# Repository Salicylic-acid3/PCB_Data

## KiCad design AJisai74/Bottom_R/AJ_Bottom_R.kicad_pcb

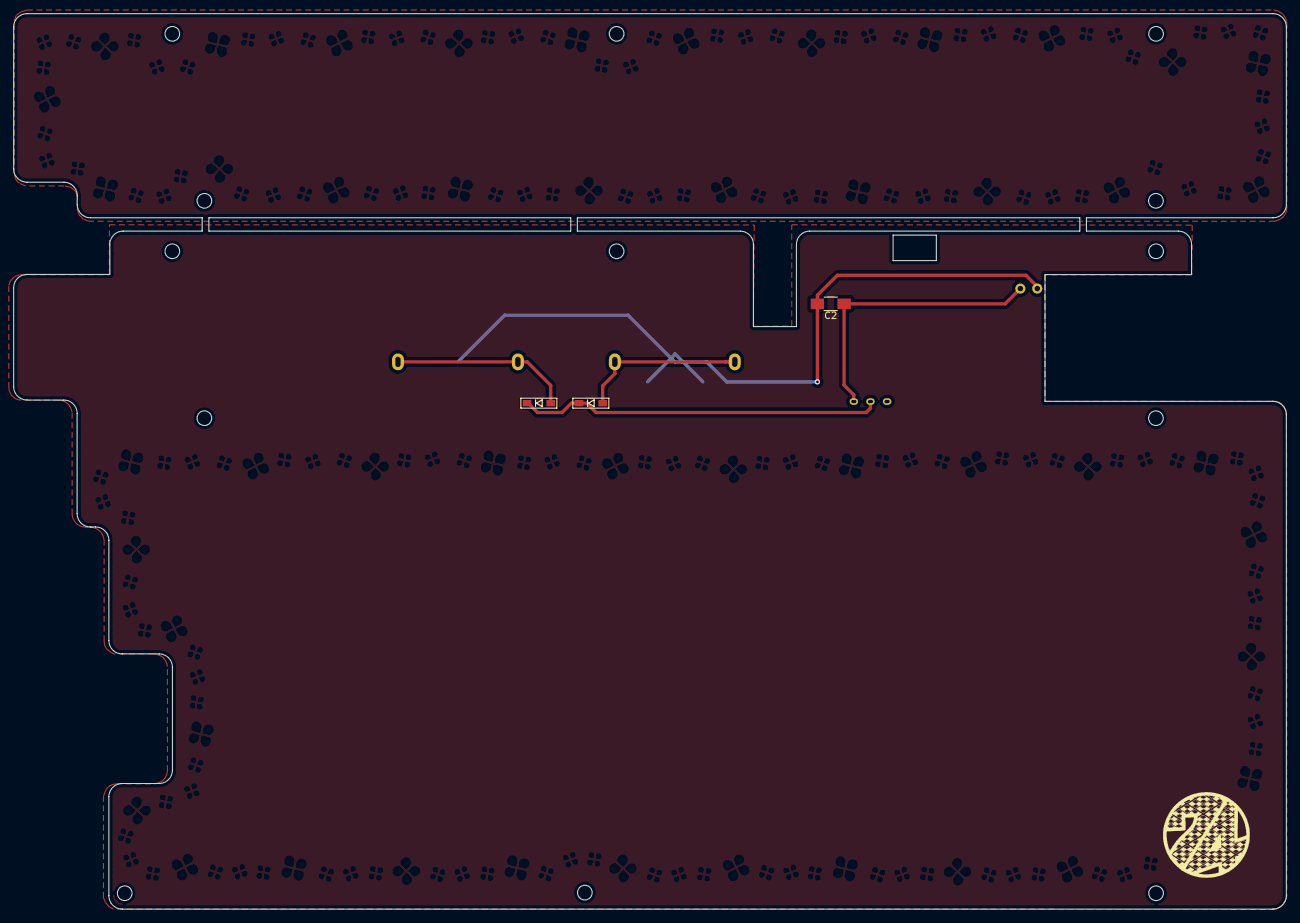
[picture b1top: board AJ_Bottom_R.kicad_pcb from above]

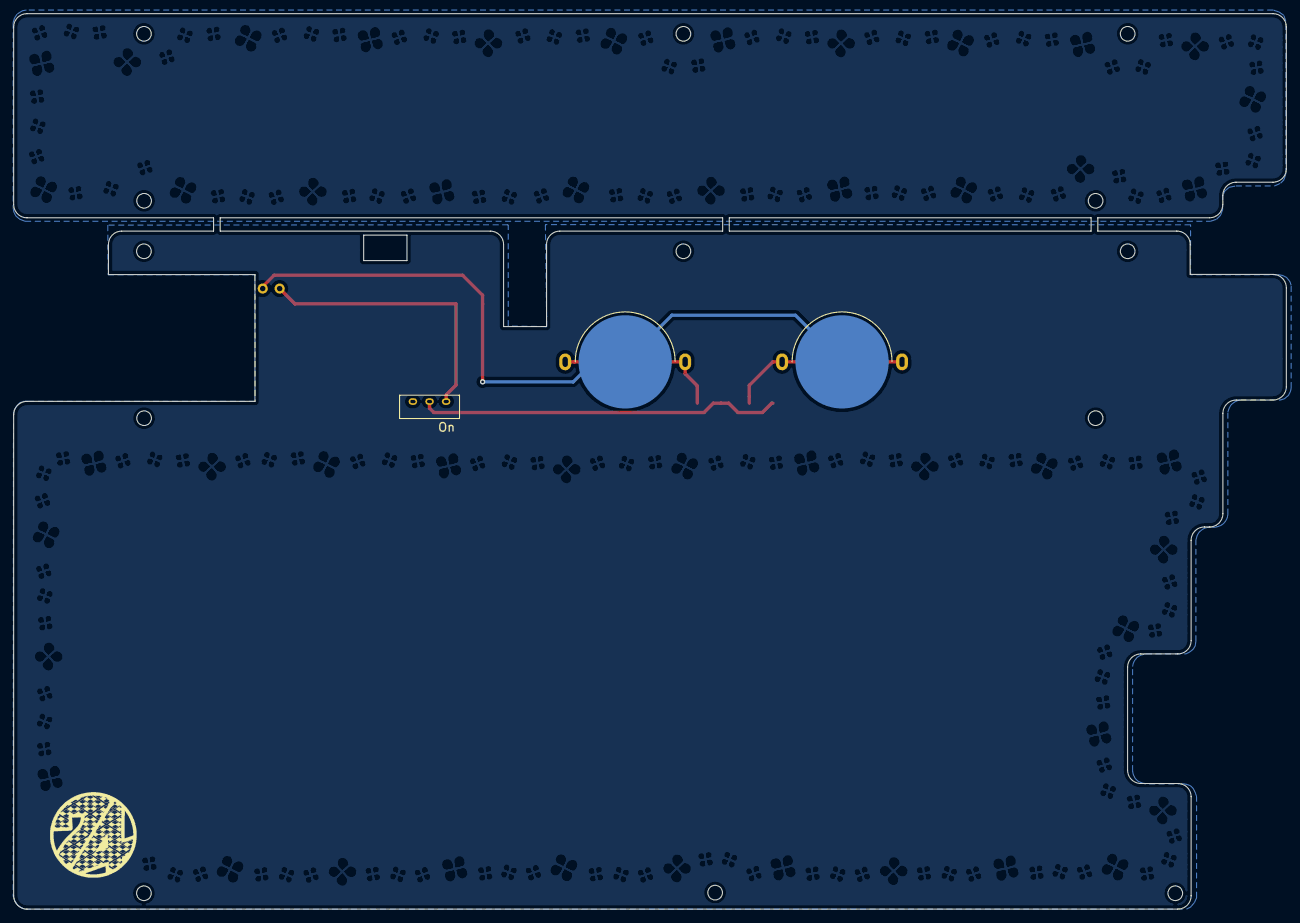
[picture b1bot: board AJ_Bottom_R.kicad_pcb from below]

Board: 2 copper layers, 191.0 x 134.4 mm, 20 parts (6 on the bottom side), 5 nets.

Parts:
BT3, BT4: Battery_Cell; ali_CR1632
C2: C_Small; C_1206_HandSoldering_Back
D3, D4: D; D3_SMD_L1
J4, J5, J13, J14, J15, J16, J18, J19, J19#2: Conn_01x01; HOLE_m2
J20: Conn_01x02; 2pinBLE
Ref**: Val**; HOLE_m2
Ref**#2, Ref**#3, Ref**#4: Val**; HOLE_m2
SW2: SW_Push_SPDT; MSK-12D19

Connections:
Bat+: C2.1, J20.1, SW2.1
GND: BT3.2, BT4.2, C2.2, J20.2
unnamed: BT3.1, D3.2
unnamed: BT4.1, D4.2
unnamed: D3.1, D4.1, SW2.2

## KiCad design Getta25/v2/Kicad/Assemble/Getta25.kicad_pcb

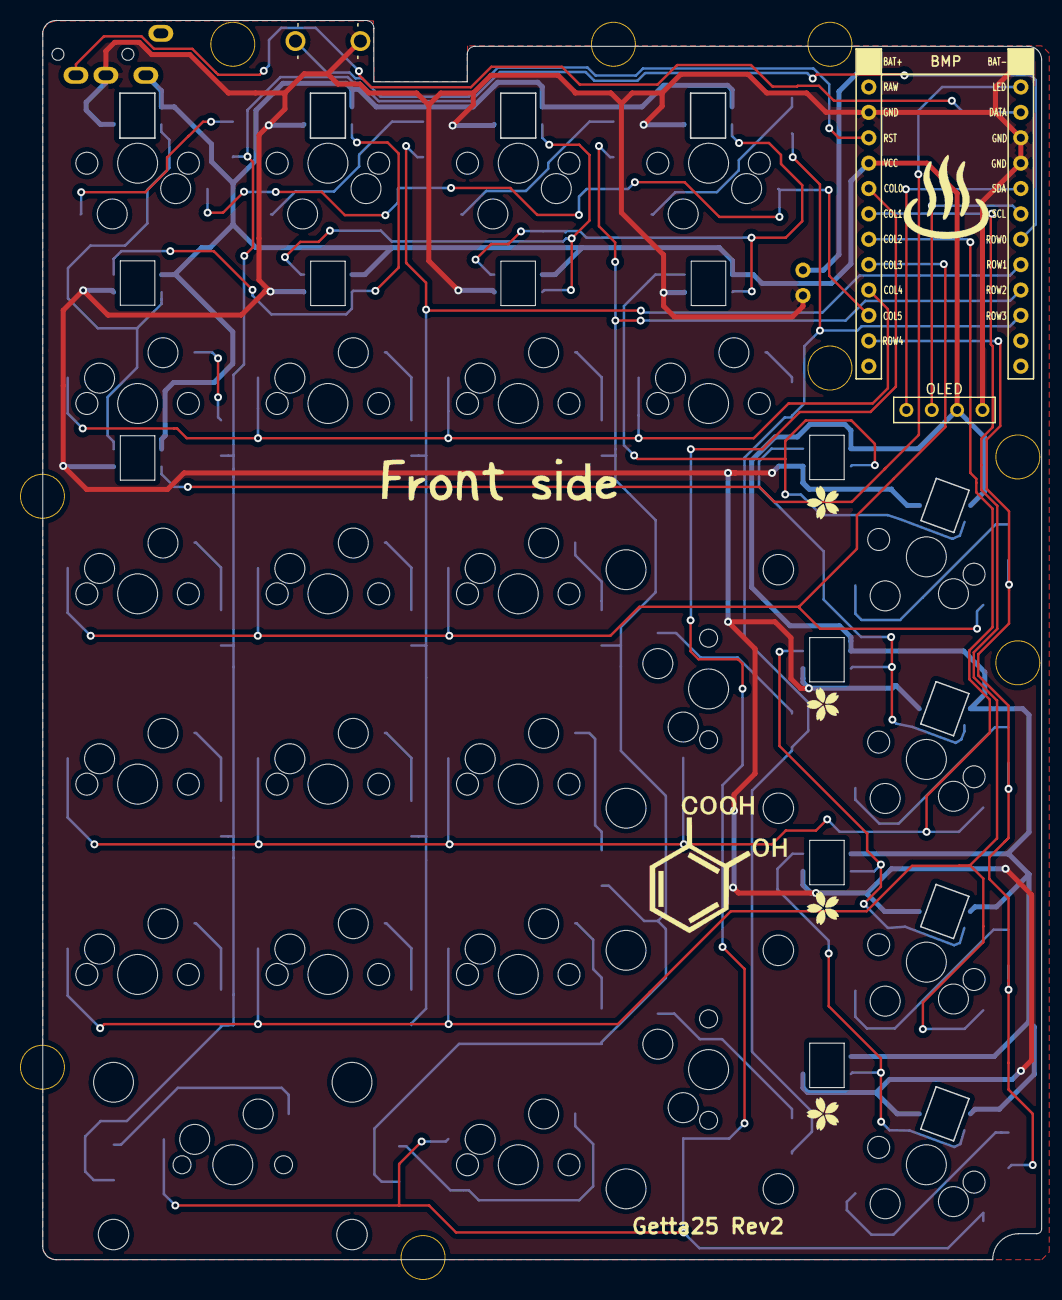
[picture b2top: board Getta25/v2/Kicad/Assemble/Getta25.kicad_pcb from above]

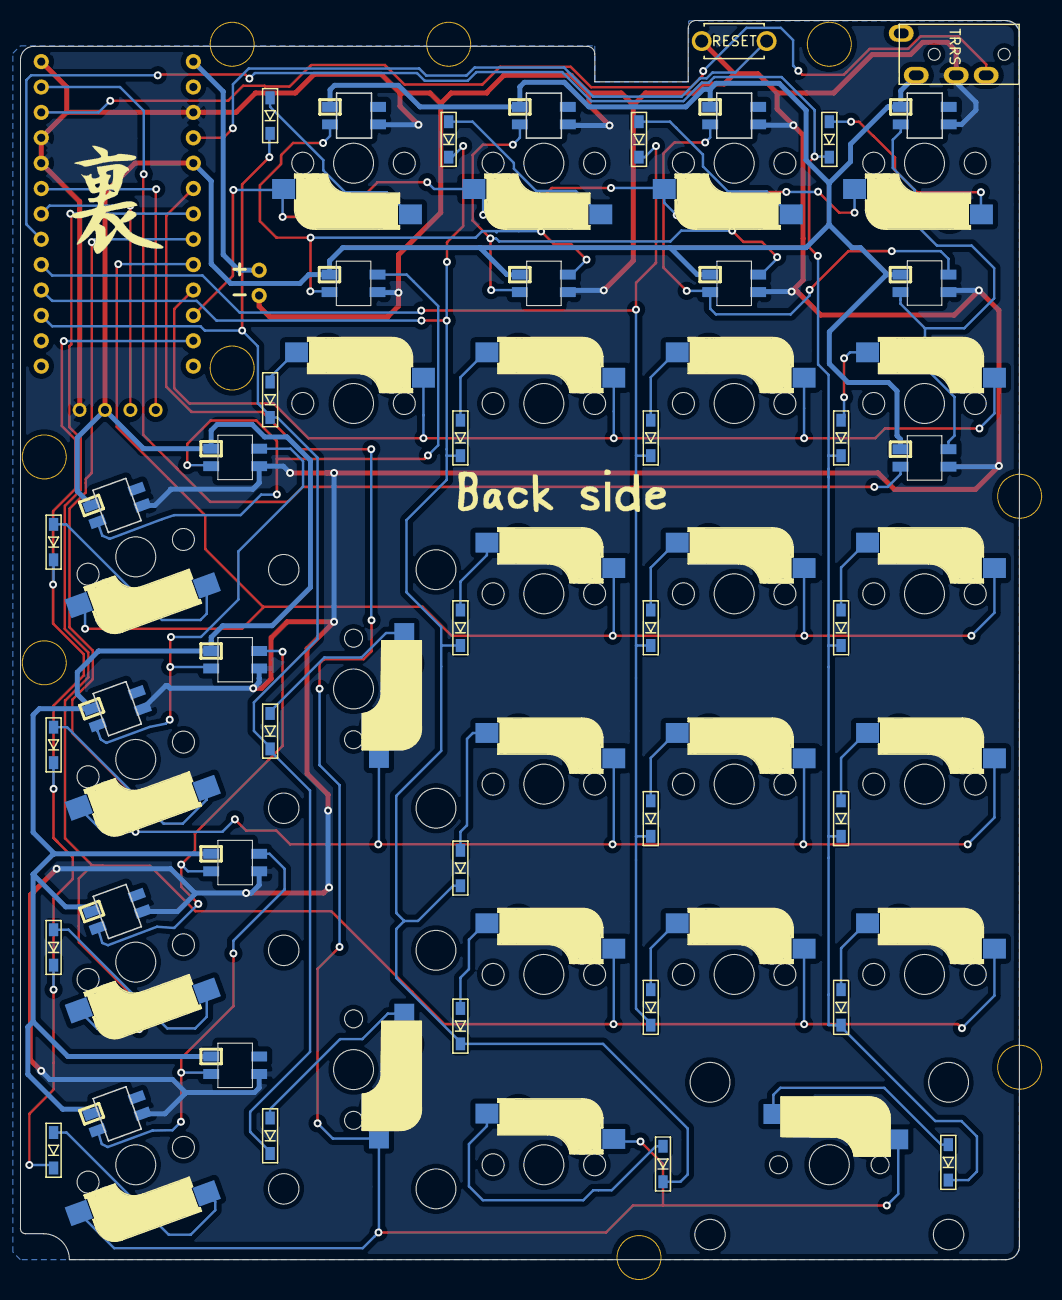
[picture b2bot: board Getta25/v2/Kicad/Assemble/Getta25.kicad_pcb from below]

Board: 2 copper layers, 100.0 x 124.0 mm, 81 parts (2 on the bottom side), 52 nets.

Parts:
D1, D2, D3, D4, D5, D6, D7, D8, D9, D10, D11, D12, D13, D14, D15, D16, D17, D18, D19, D20, D21, D22, D23, D24, D25: D; D3_SMD_L1
J1: MJ-4PP-9; MJ-4PP-9_1L
J2: Conn_01x04; OLED_FL
J3: Conn_01x02; 2pinBLE
J6, J6#2, J6#3, J7, J8, J10, J11, J12, J13: Conn_01x01; HOLE_giri
L1, L2, L3, L4, L5, L6, L7, L8, L9, L10, L11, L12, L13, L14, L15, L16, L17: SK6812MINI; SK6812MINI_rev_BL
SW1, SW3, SW12: SW_PUSH; CherryMX_Hotswap_2u_BL_SF
SW2, SW4, SW5, SW6, SW7, SW8, SW9, SW10, SW11, SW13, SW14, SW15, SW16, SW17, SW18, SW19, SW20, SW21, SW22, SW23, SW24, SW25: SW_PUSH; CherryMX_Hotswap_BL_LH
SW26: SW_PUSH; ResetSW_FL
U1: BLEMicroPro; BLE_Micro_Pro_L1

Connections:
Bat+: J3.1, U1.25
Col0: SW1.1, SW2.1, SW3.1, SW4.1, U1.20
Col1: SW5.1, SW6.1, SW7.1, SW8.1, U1.19
Col2: SW9.1, SW10.1, SW11.1, SW12.1, SW13.1, U1.18
Col3: SW14.1, SW15.1, SW16.1, SW17.1, U1.17
Col4: SW18.1, SW19.1, SW20.1, SW21.1, U1.16
Col5: SW22.1, SW23.1, SW24.1, SW25.1, U1.15
Data: J1.B, U1.2
GND: J1.C, J2.4, J3.2, L1.2, L2.2, L3.2, L4.2, L5.2, L6.2, L7.2, L8.2, L9.2, L10.2, L11.2, L12.2, L13.2, L14.2, L15.2, L16.2, L17.2, SW26.2, U1.3, U1.4, U1.23, U1.26
unnamed: D1.2, SW1.2
unnamed: D2.2, SW2.2
unnamed: D3.2, SW3.2
unnamed: D4.2, SW4.2
unnamed: D5.2, SW5.2
unnamed: D6.2, SW6.2
unnamed: D7.2, SW7.2
unnamed: D8.2, SW8.2
unnamed: D9.2, SW9.2
unnamed: D10.2, SW10.2
unnamed: D11.2, SW11.2
unnamed: D12.2, SW12.2
unnamed: D13.2, SW13.2
unnamed: D14.2, SW14.2
unnamed: D15.2, SW15.2
unnamed: D16.2, SW16.2
unnamed: D17.2, SW17.2
unnamed: D18.2, SW18.2
unnamed: D19.2, SW19.2
unnamed: D20.2, SW20.2
unnamed: D21.2, SW21.2
unnamed: D22.2, SW22.2
unnamed: D23.2, SW23.2
unnamed: D24.2, SW24.2
unnamed: D25.2, SW25.2
unnamed: L1.1, L2.3, L15.3
unnamed: L4.1, L5.3, L11.3
unnamed: L5.1, L6.3, L12.3
unnamed: L6.1, L7.3, L13.3
unnamed: L7.1, L8.3, L14.3
unnamed: L2.1, L3.3, L16.3
unnamed: L3.1, L4.3, L17.3
Reset: SW26.1, U1.22
Row0: D1.1, D5.1, D9.1, D14.1, D18.1, D22.1, U1.7
Row1: D6.1, D10.1, D15.1, D19.1, D23.1, U1.8
Row2: D2.1, D7.1, D11.1, D16.1, D20.1, D24.1, U1.9
Row3: D3.1, D12.1, D21.1, D25.1, U1.10
Row4: D4.1, D8.1, D13.1, D17.1, U1.14
SCL: J2.2, U1.6
SDA: J2.1, U1.5
VCC: J1.D, J2.3, L1.4, L2.4, L3.4, L4.4, L5.4, L6.4, L7.4, L8.4, L9.4, L10.4, L11.4, L12.4, L13.4, L14.4, L15.4, L16.4, L17.4, U1.21
led: L9.3, U1.1
to1: L1.3, L9.1, L10.3

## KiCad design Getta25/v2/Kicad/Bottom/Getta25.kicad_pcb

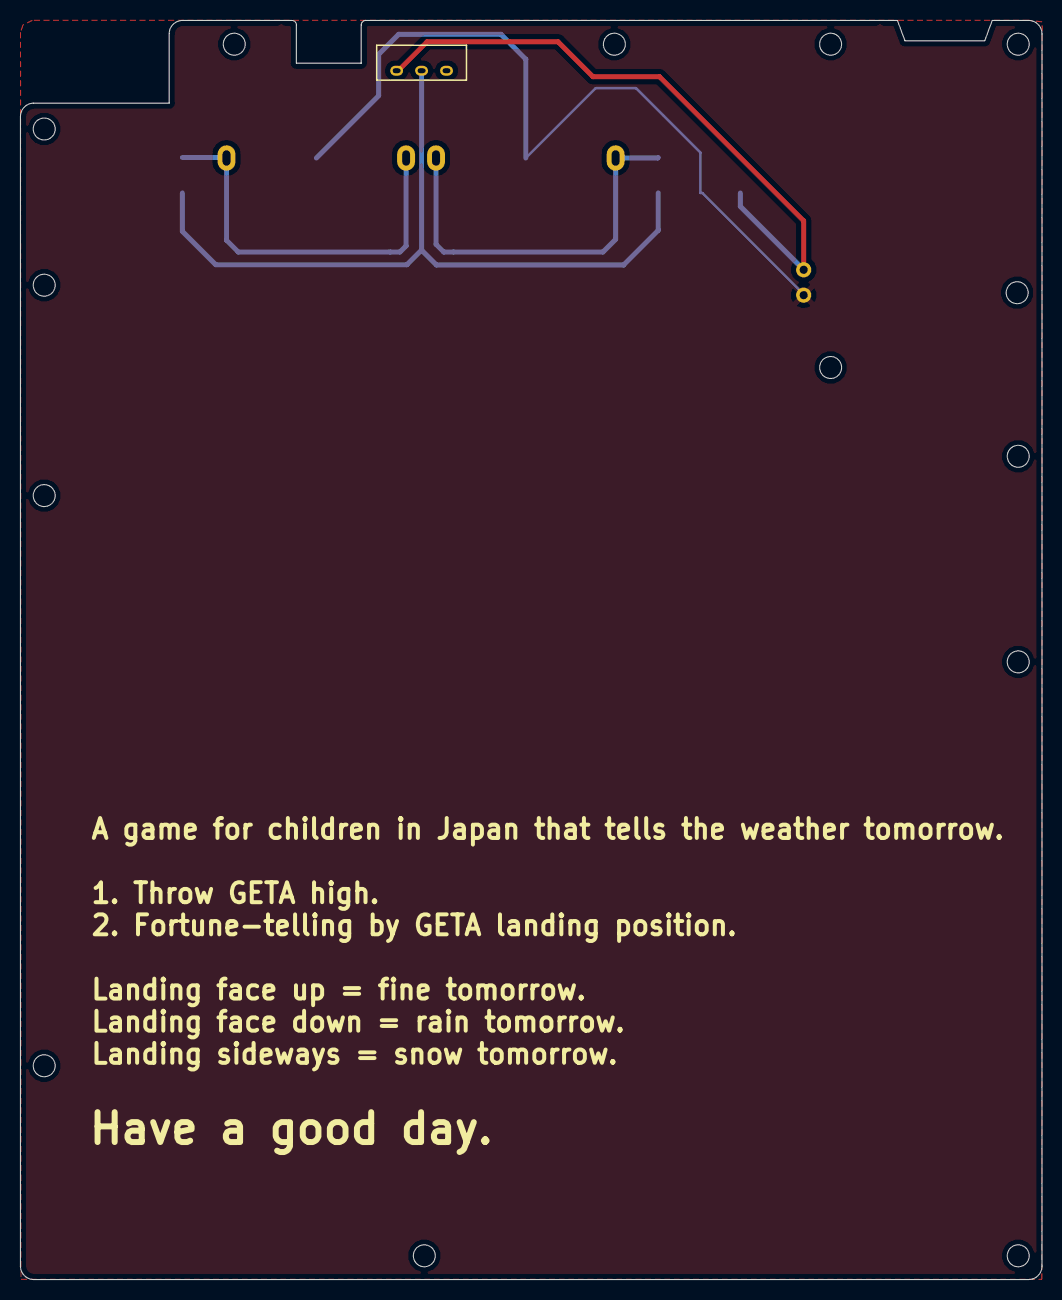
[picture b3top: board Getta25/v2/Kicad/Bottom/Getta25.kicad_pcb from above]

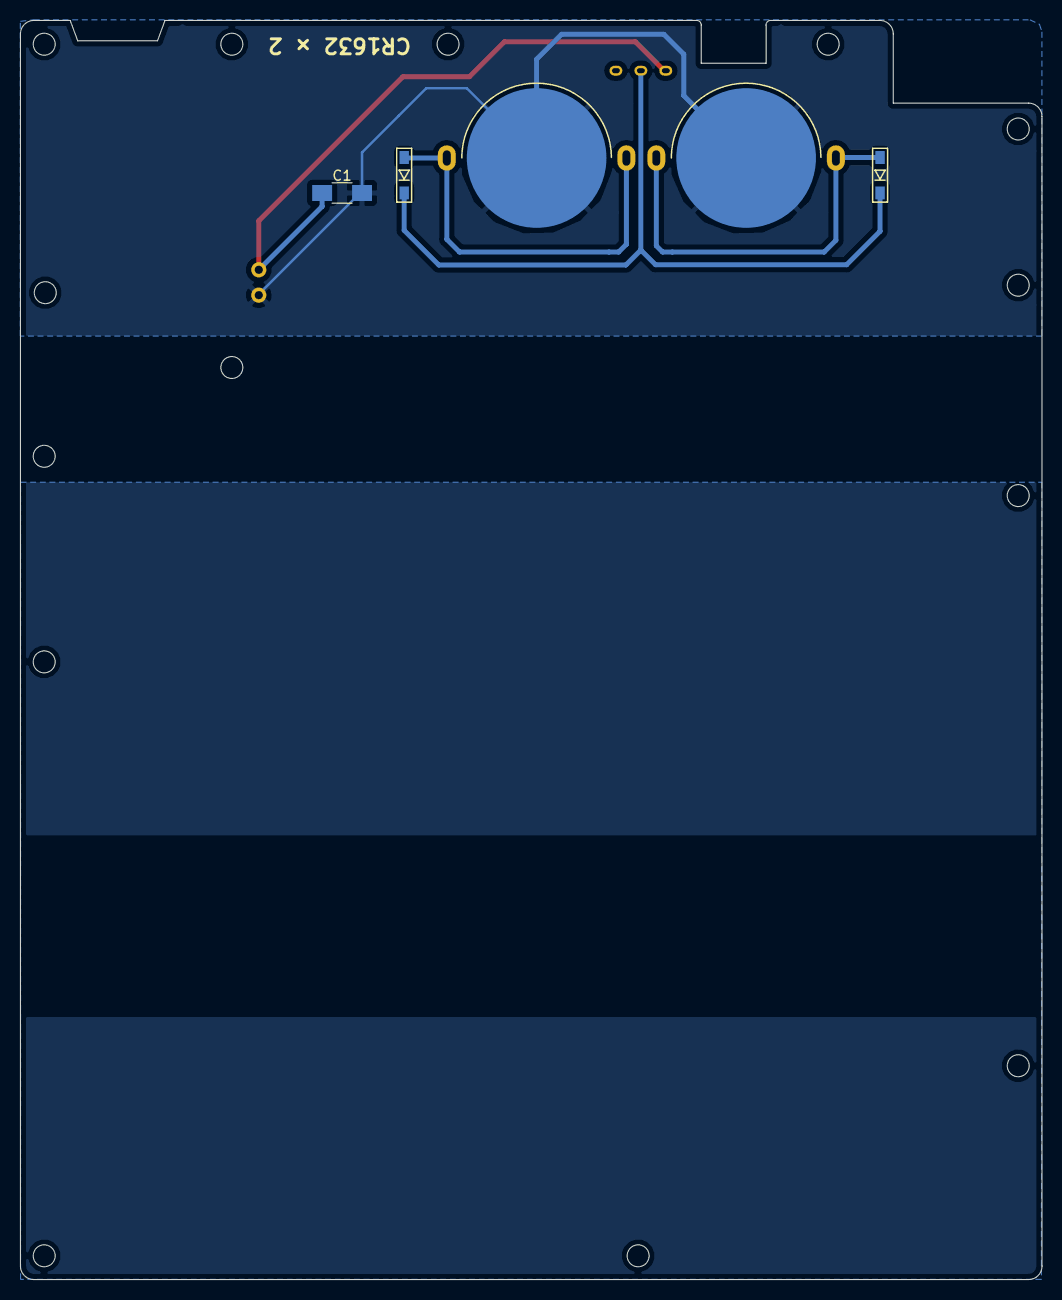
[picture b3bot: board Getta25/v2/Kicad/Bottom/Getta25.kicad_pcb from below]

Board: 2 copper layers, 102.4 x 126.2 mm, 21 parts (2 on the bottom side), 5 nets.

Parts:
BT1, BT2: Battery_Cell; ali_CR1632
C1: C_Small; C_1206_HandSoldering_Back
D1, D2: D; D3_SMD_L1
J1: Conn_01x02; 2pinBLE
J3, J4, J5, J6, J7, J8, J9, J11, J12, J13, J16, J17, J18, J19: Conn_01x01; HOLE_m2
SW1: SW_Push_SPDT; MSK-12D19

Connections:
Bat+: C1.1, J1.1, SW1.1
GND: BT1.2, BT2.2, C1.2, J1.2
unnamed: BT1.1, D1.2
unnamed: BT2.1, D2.2
unnamed: D1.1, D2.1, SW1.2
